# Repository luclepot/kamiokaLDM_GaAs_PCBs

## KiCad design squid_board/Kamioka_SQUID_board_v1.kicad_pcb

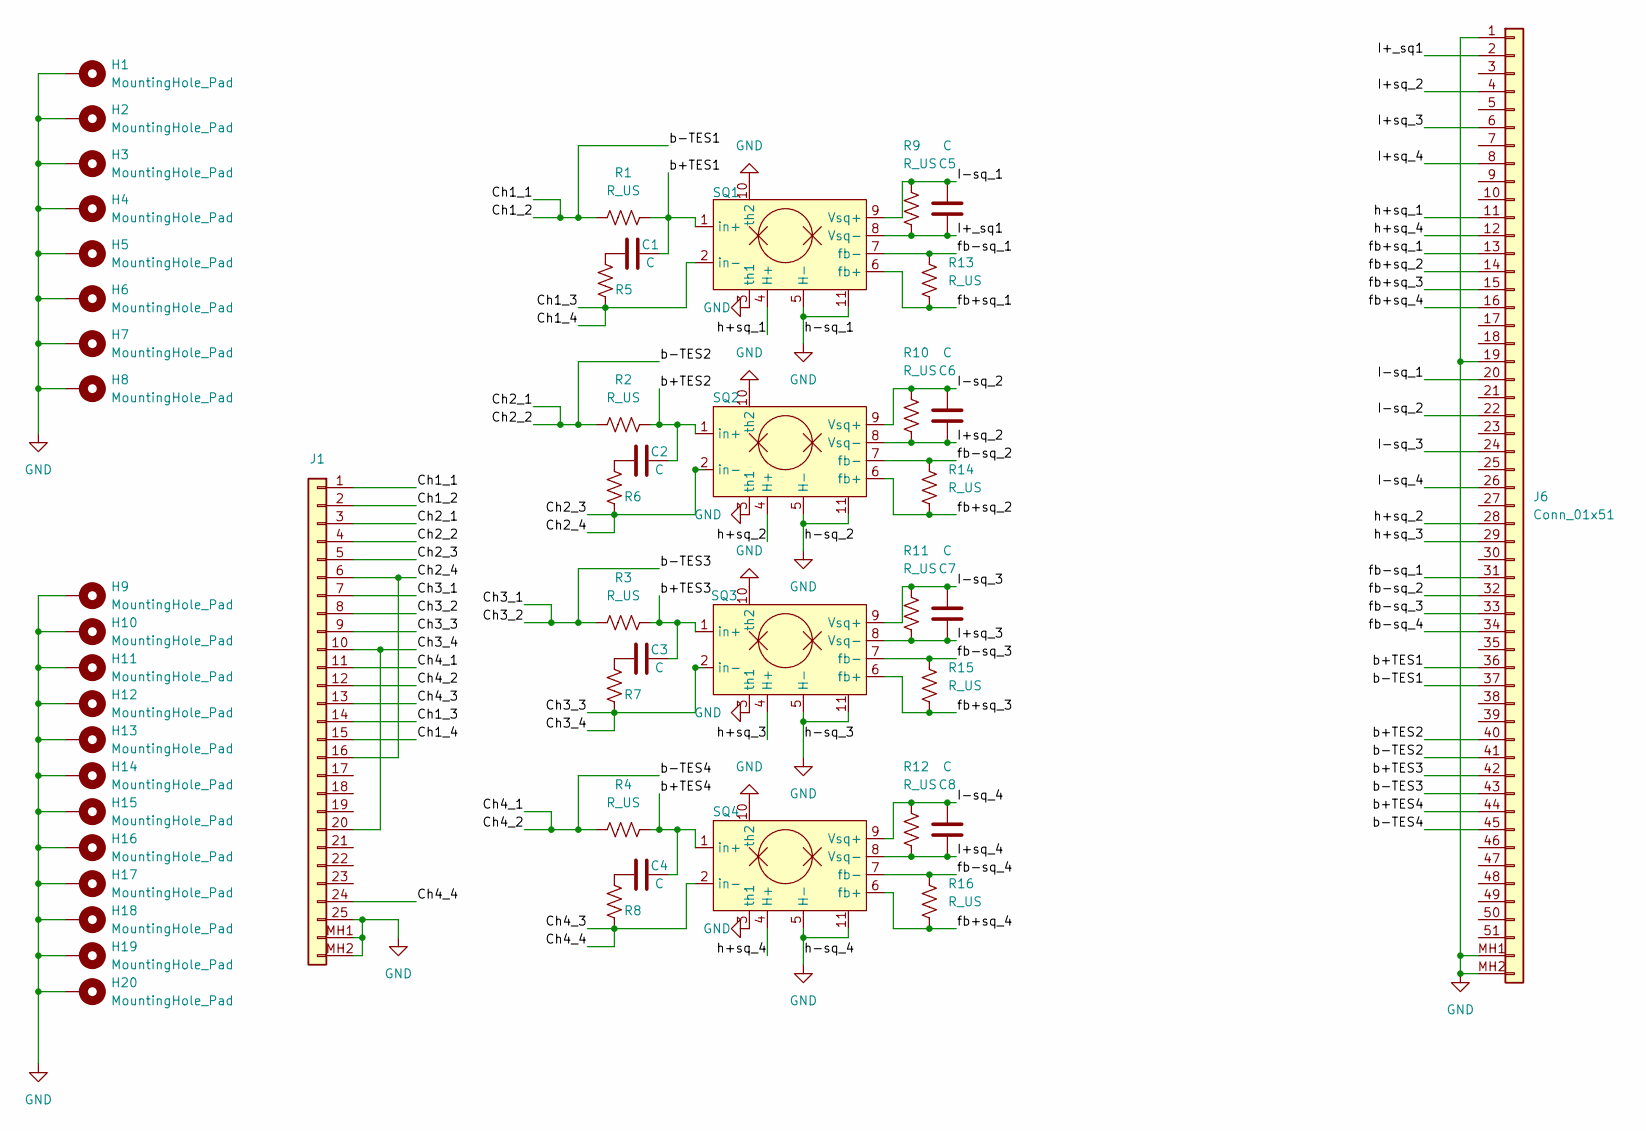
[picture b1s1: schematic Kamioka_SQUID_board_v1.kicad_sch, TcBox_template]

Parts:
C1, C2, C3, C4, C5, C6, C7, C8: C; C_0805_2012Metric
H1, H2, H3, H4, H5, H6, H7, H8: MountingHole_Pad; M3_mountHole
H9, H10, H11, H12, H13, H14, H15, H16, H17, H18, H19, H20: MountingHole_Pad; MountingHole_2.2mm_M2_DIN965_Pad_TopBottom
J1: Conn_01x25; MDM25-SBSP
J6: Conn_01x51; MDM51SBSP
R1, R2, R3, R4: R_US; RESC2012X60N
R5, R6, R7, R8: R_US; R_0805_2012Metric
R9, R10, R11, R12, R13, R14, R15, R16: R_US; C_0805_2012Metric
SQ1, SQ2, SQ3, SQ4: SQ1550

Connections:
/Ch1_1: J1.1, J1.2, J6.37, R1.1
/Ch1_3: J1.14, J1.15, R5.2, SQ1.2 (in-)
/Ch2_1: J1.3, J1.4, J6.41, R2.1
/Ch2_3: J1.5, J1.6, J1.16, R6.2, SQ2.2 (in-)
/Ch3_1: J1.7, J1.8, J6.43, R3.1
/Ch3_3: J1.9, J1.10, J1.20, R7.2, SQ3.2 (in-)
/Ch4_1: J1.11, J1.12, J6.45, R4.1
/Ch4_3: J1.13, J1.24, R8.2, SQ4.2 (in-)
/I+_sq1: C5.1, J6.2, R9.2, SQ1.8 (Vsq-)
/I+sq_2: C6.1, J6.4, R10.2, SQ2.8 (Vsq-)
/I+sq_3: C7.1, J6.6, R11.2, SQ3.8 (Vsq-)
/I+sq_4: C8.1, J6.8, R12.2, SQ4.8 (Vsq-)
/I-sq_1: C5.2, J6.20, R9.1, SQ1.9 (Vsq+)
/I-sq_2: C6.2, J6.22, R10.1, SQ2.9 (Vsq+)
/I-sq_3: C7.2, J6.24, R11.1, SQ3.9 (Vsq+)
/I-sq_4: C8.2, J6.26, R12.1, SQ4.9 (Vsq+)
/b+TES1: C1.2, J6.36, R1.2, SQ1.1 (in+)
/b+TES2: C2.2, J6.40, R2.2, SQ2.1 (in+)
/b+TES3: C3.2, J6.42, R3.2, SQ3.1 (in+)
/b+TES4: C4.2, J6.44, R4.2, SQ4.1 (in+)
/fb+sq_1: J6.13, R13.1, SQ1.6 (fb+)
/fb+sq_2: J6.14, R14.1, SQ2.6 (fb+)
/fb+sq_3: J6.15, R15.1, SQ3.6 (fb+)
/fb+sq_4: J6.16, R16.1, SQ4.6 (fb+)
/fb-sq_1: J6.31, R13.2, SQ1.7 (fb-)
/fb-sq_2: J6.32, R14.2, SQ2.7 (fb-)
/fb-sq_3: J6.33, R15.2, SQ3.7 (fb-)
/fb-sq_4: J6.34, R16.2, SQ4.7 (fb-)
/h+sq_1: J6.11, SQ1.4 (H+)
/h+sq_2: J6.28, SQ2.4 (H+)
/h+sq_3: J6.29, SQ3.4 (H+)
/h+sq_4: J6.12, SQ4.4 (H+)
GND: H1.1 (1_1), H2.1 (1_1), H3.1 (1_1), H4.1 (1_1), H5.1 (1_1), H6.1 (1_1), H7.1 (1_1), H8.1 (1_1), H9.1 (1_1), H10.1 (1_1), H11.1 (1_1), H12.1 (1_1), H13.1 (1_1), H14.1 (1_1), H15.1 (1_1), H16.1 (1_1), H17.1 (1_1), H18.1 (1_1), H19.1 (1_1), H20.1 (1_1), J1.25, J1.MH1 (Pin_26), J1.MH2 (Pin_27), J6.1, J6.19, J6.MH1 (Pin_52), J6.MH2 (Pin_53), SQ1.3 (th1), SQ1.5 (H-), SQ1.10 (th2), SQ1.11, SQ2.3 (th1), SQ2.5 (H-), SQ2.10 (th2), SQ2.11, SQ3.3 (th1), SQ3.5 (H-), SQ3.10 (th2), SQ3.11, SQ4.3 (th1), SQ4.5 (H-), SQ4.10 (th2), SQ4.11
unnamed: C1.1, R5.1
unnamed: C2.1, R6.1
unnamed: C3.1, R7.1
unnamed: C4.1, R8.1

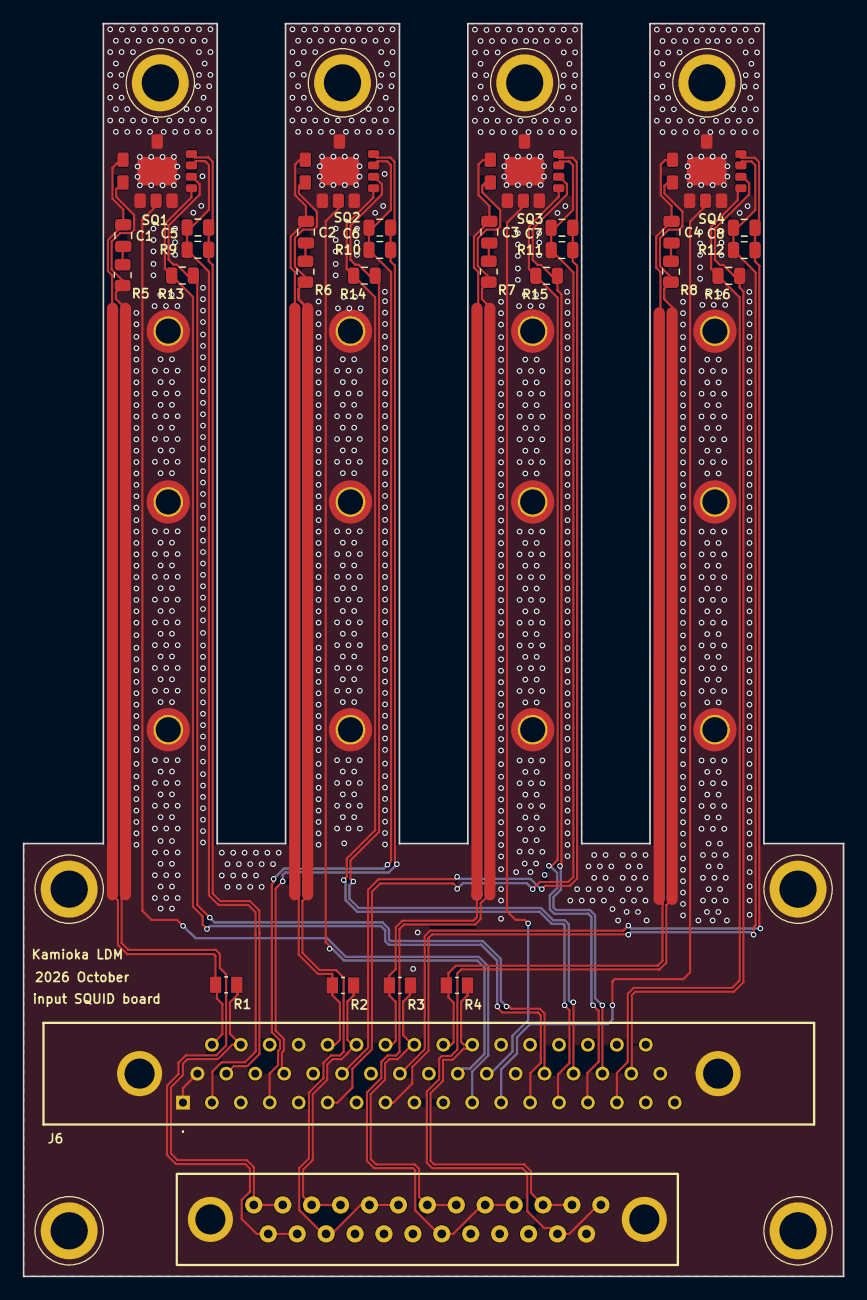
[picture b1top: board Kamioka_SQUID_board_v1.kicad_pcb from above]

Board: 2 copper layers, 72.0 x 110.0 mm, 50 parts (0 on the bottom side), 37 nets.

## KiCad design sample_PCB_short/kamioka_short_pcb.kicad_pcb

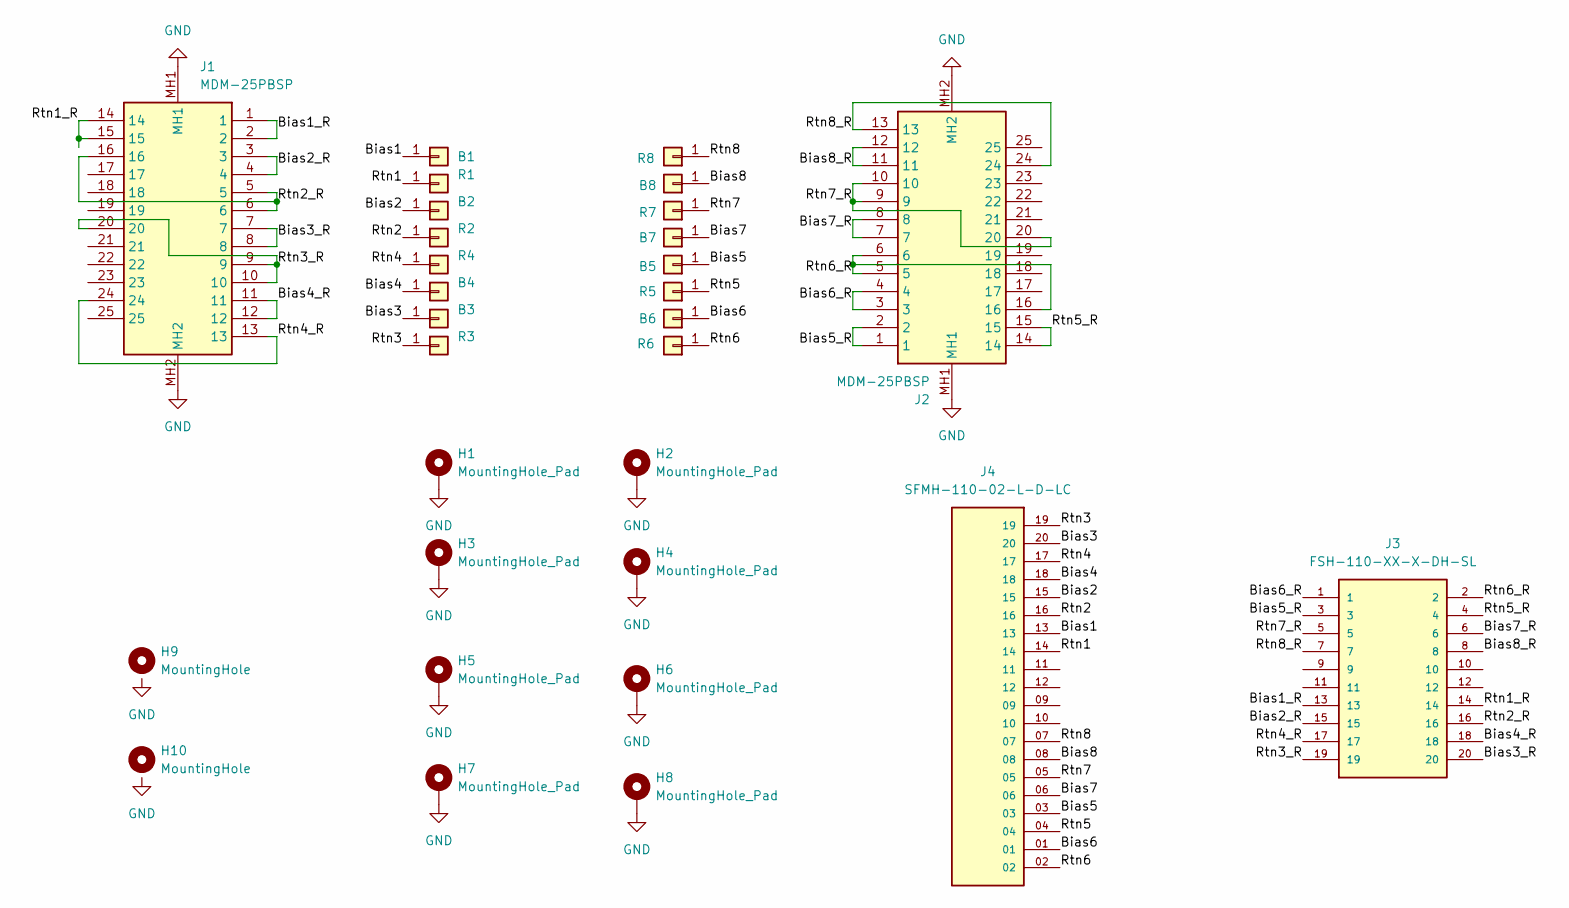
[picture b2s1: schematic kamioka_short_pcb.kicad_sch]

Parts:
B1, B2, B3, B4, B5, B6, B7, B8: Conn_01x01; SolderWirePad_1x01_SMD_0.5x1mm
H1, H2, H3, H4, H5, H6, H7, H8: MountingHole_Pad; MountingHole_2.2mm_M2_ISO7380_Pad_TopOnly
H9, H10: MountingHole; MountingHole_6.4mm_M6_DIN965_Pad_TopBottom
J1, J2: MDM-25PBSP; MDM25PBSP; Mouser Part Number 965-MDM-25PBSP
J3: FSH-110-XX-X-DH-SL; SAMTEC_FSH-110-XX-X-DH-SL; PARTREV G
J4: SFMH-110-02-L-D-LC; SAMTEC_SFMH-110-02-L-D-LC; PARTREV E
R1, R2, R3, R4, R5, R6, R7, R8: Conn_01x01; SolderWirePad_1x01_SMD_0.5x1mm

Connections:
/Bias1: B1.1, J4.13
/Bias1_R: J1.1, J1.2, J3.13
/Bias2: B2.1, J4.15
/Bias2_R: J1.3, J1.4, J3.15
/Bias3: B3.1, J4.20
/Bias3_R: J1.7, J1.8, J3.20
/Bias4: B4.1, J4.18
/Bias4_R: J1.11, J1.12, J3.18
/Bias5: B5.1, J4.03
/Bias5_R: J2.1, J2.2, J3.3
/Bias6: B6.1, J4.01
/Bias6_R: J2.3, J2.4, J3.1
/Bias7: B7.1, J4.06
/Bias7_R: J2.7, J2.8, J3.6
/Bias8: B8.1, J4.08
/Bias8_R: J2.11, J2.12, J3.8
/Rtn1: J4.14, R1.1
/Rtn1_R: J1.14, J1.15, J3.14
/Rtn2: J4.16, R2.1
/Rtn2_R: J1.5, J1.6, J1.16, J3.16
/Rtn3: J4.19, R3.1
/Rtn3_R: J1.9, J1.10, J1.20, J3.19
/Rtn4: J4.17, R4.1
/Rtn4_R: J1.13, J1.24, J3.17
/Rtn5: J4.04, R5.1
/Rtn5_R: J2.14, J2.15, J3.4
/Rtn6: J4.02, R6.1
/Rtn6_R: J2.5, J2.6, J2.16, J3.2
/Rtn7: J4.05, R7.1
/Rtn7_R: J2.9, J2.10, J2.20, J3.5
/Rtn8: J4.07, R8.1
/Rtn8_R: J2.13, J2.24, J3.7
GND: H1.1, H2.1, H3.1, H4.1, H5.1, H6.1, H7.1, H8.1, J1.MH1, J1.MH2, J2.MH1, J2.MH2

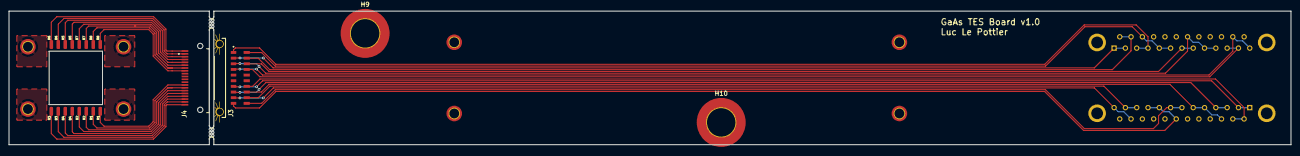
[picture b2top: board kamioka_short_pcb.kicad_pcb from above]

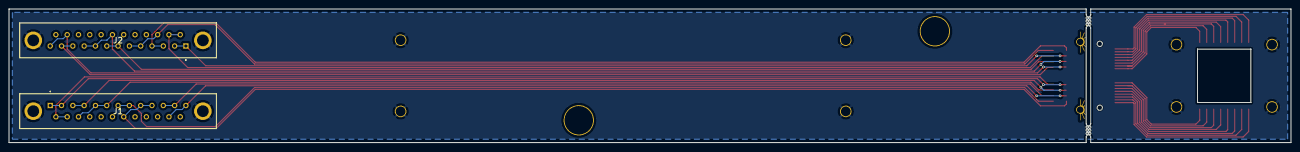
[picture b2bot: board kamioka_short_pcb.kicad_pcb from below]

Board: 2 copper layers, 288.0 x 30.0 mm, 32 parts (2 on the bottom side), 33 nets.

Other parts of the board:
mouse-bite-1mm-3mm, mouse-bite-1mm-3mm#2: VAL**; mouse-bite-1mm-3mm
